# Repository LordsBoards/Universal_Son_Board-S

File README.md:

# Uninversal sonboard series #1 slim

I changed a bunch of stuff on the series s UDB because some design changes were needed
- Back to the old JST. Pico EZMate is rated for too few mating cycles
- Different USB routing. I wouldn't recommend running anything higher than USB fullspeed (12mbps) over a long jst w/o shielding. pls don't run high speed usb over a daughterboard
- Different parts. The USBLC6 I used lets you get away without an external ESD diode on your power/ground lines
- Added some mousebites. should be easier to panelize 
- Some smaller footprints
- Changed to the way cooler squiggly U.S. resistor symbol 🦅🇺🇸🦅🇺🇸🦅🇺🇸🦅🇺🇸

Everything should be just as available on JLC so hav fun =^)

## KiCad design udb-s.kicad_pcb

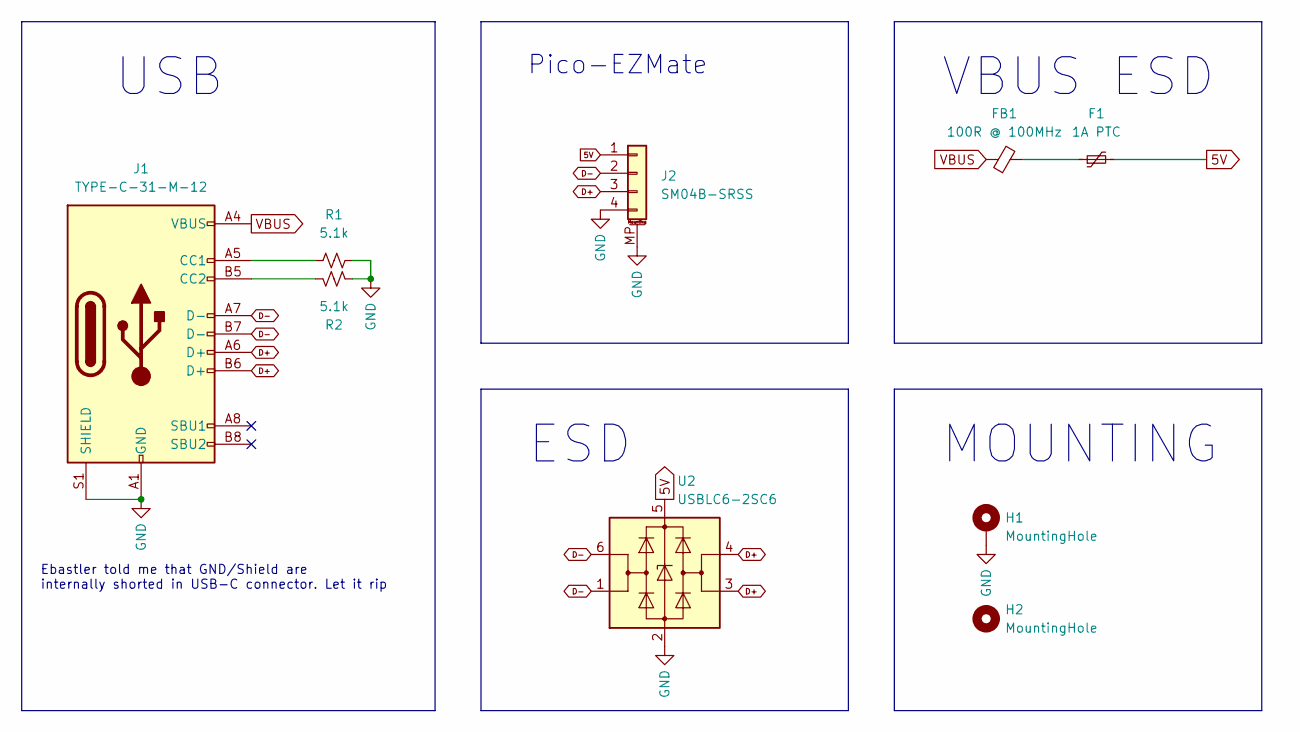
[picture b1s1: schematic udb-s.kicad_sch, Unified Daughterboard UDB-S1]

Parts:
F1: 1A PTC; Fuse_0402_1005Metric; LCSC Part Number C914087
FB1: 100R @ 100MHz; L_0603_1608Metric; LCSC Part Number C96995
H1: MountingHole; MountingHole_3.2mm_M3_DIN965_Pad_TopBottom
H2: MountingHole; MountingHole_3.2mm_M3_DIN965_Pad_TopOnly
J1: TYPE-C-31-M-12; USB_C_Receptacle_HRO_TYPE-C-31-M-12; Manufacturer Part Number TYPE-C-31-M-12; LCSC Part Number C165948
J2: SM04B-SRSS; JST_SH_SM04B-SRSS-TB_1x04-1MP_P1.00mm_Horizontal; Manufacturer Part Number SM04B-SRSS-TB; LCSC Part Number C160404
R1, R2: 5.1k; R_0402_1005Metric; LCSC Part Number C105872
U2: USBLC6-2SC6; SOT-23-6; Manufacturer Part Number Many; LCSC Part Number C2827654

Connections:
5V: F1.2, J2.1, U2.5 (VBUS)
D+: J1.A6 (D+), J1.B6 (D+), J2.3, U2.3 (I/O2), U2.4 (I/O2)
D-: J1.A7 (D-), J1.B7 (D-), J2.2, U2.1 (I/O1), U2.6 (I/O1)
GND: H1.1, J1.A1 (GND), J1.A12 (GND), J1.B1 (GND), J1.B12 (GND), J1.S1 (SHIELD), J2.4, J2.MP (MountPin), R1.2, R2.2, U2.2 (GND)
unnamed: F1.1, FB1.2
unnamed: J1.A5 (CC1), R1.1
unnamed: J1.B5 (CC2), R2.1
VBUS: FB1.1, J1.A4 (VBUS), J1.A9 (VBUS), J1.B4 (VBUS), J1.B9 (VBUS)

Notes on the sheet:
ESD
VBUS ESD
Ebastler told me that GND/Shield are internally shorted in USB-C connector. Let it rip
USB
MOUNTING
Pico-EZMate

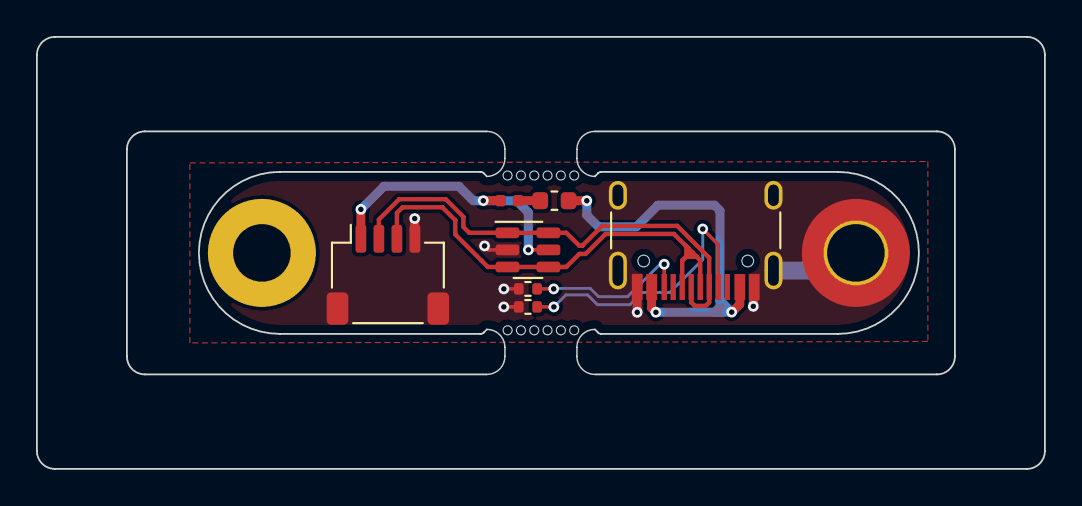
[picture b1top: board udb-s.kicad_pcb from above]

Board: 4 copper layers, 56.0 x 24.0 mm, 9 parts (0 on the bottom side), 8 nets.

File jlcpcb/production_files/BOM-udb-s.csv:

Comment,Designator,Footprint,LCSC
5.1k,"R1,R2",R_0402_1005Metric,C105872
SM04B-SRSS,J2,JST_SH_SM04B-SRSS-TB_1x04-1MP_P1.00mm_Horizontal,C160404
TYPE-C-31-M-12,J1,USB_C_Receptacle_HRO_TYPE-C-31-M-12,C165948
USBLC6-2SC6,U2,SOT-23-6,C2827654
1A PTC,F2,Fuse_0402_1005Metric,C914087
100R @ 100MHz,FB1,L_0603_1608Metric,C96995

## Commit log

2023-07-28 Redesigned
2023-07-28 Update LICENSE
2023-08-06 changed the layout so it can be assembled by jlc :)
2023-08-26 Adjusted ferrite bead location and changed mousebites
2023-12-01 Modified board edges for easier panelization by JLC. Changed 5.1k resistor value.
